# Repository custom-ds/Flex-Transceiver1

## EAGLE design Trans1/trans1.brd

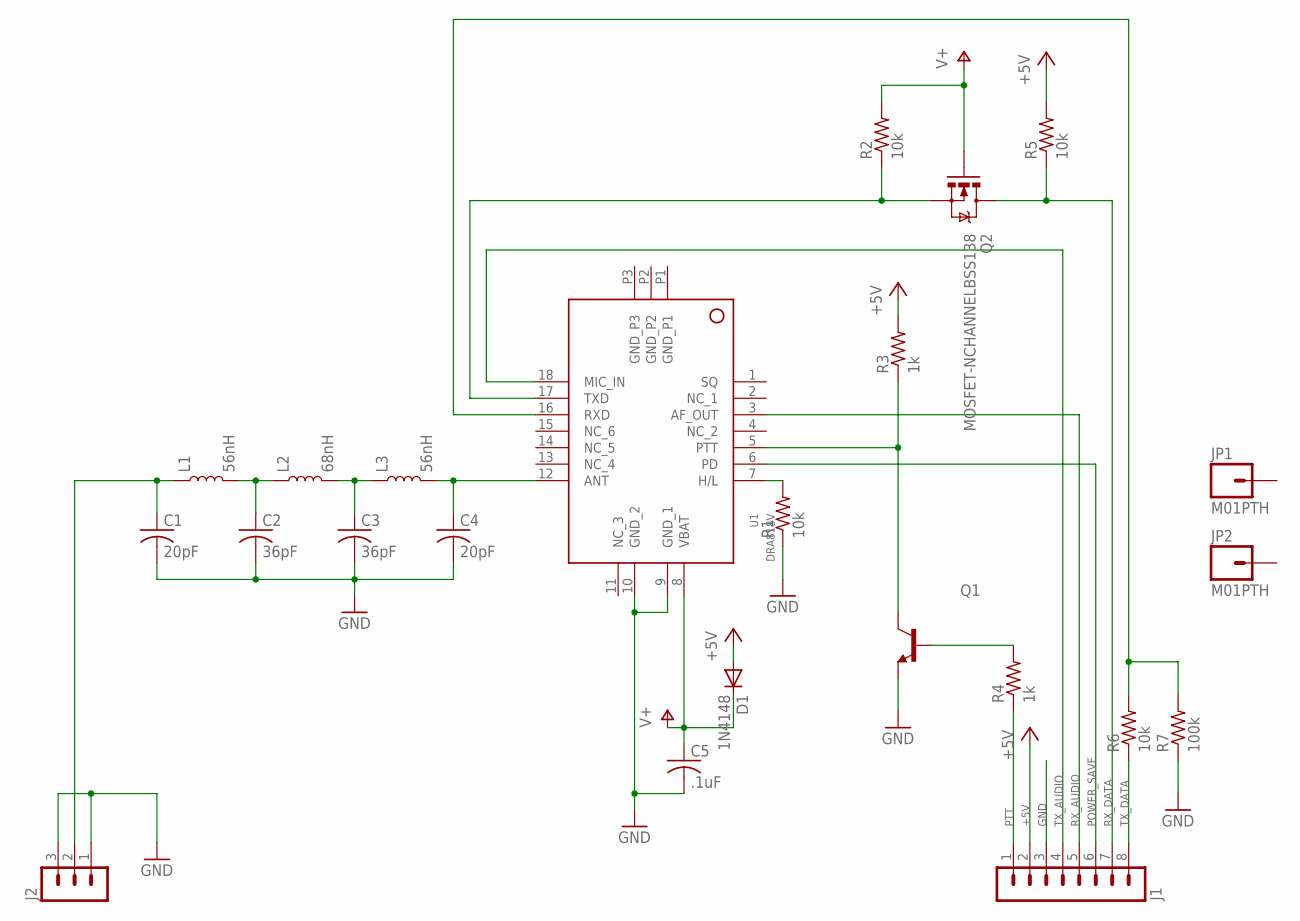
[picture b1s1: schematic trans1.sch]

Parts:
C1, C4: 20pF; C0805; DIGIKEY ‎712-1381-1-ND‎
C2, C3: 36pF; C0805; DIGIKEY 478-10473-1-ND
C5: .1uF; C0805
D1: 1N4148; SOD123
J1: MA08-1
J2: MA03-1
JP1, JP2: M01PTH; 1X01
L1, L3: 56nH; L0805; DIGIKEY 535-11570-1-ND
L2: 68nH; L0805; DIGIKEY ‎535-11572-1-ND‎
Q1: BC817-16LT1SMD; SOT23-BEC; DIGIKEY MMBT2222AFSCT-ND
Q2: MOSFET-NCHANNELBSS138; SOT23
R1, R2, R5, R6: 10k; R0805
R3, R4: 1k; R0805
R7: 100k; R0805
U1: DRA818V; SMD_DRA818

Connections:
+5V: D1.A, J1.2, R3.2, R5.2
GND: C1.2, C2.2, C3.2, C4.2, C5.2, J1.3, J2.1, J2.3, Q1.E, R1.1, R7.1, U1.9 (GND_1), U1.10 (GND_2)
unnamed: Q1.C, R3.1, U1.5 (PTT)
unnamed: R1.2, U1.7 (H/L)
unnamed: R6.2, R7.2, U1.16 (RXD)
unnamed: Q2.2 (S), R2.1, U1.17 (TXD)
unnamed: Q1.B, R4.2
unnamed: C4.1, L3.2, U1.12 (ANT)
unnamed: C3.1, L2.2, L3.1
unnamed: C2.1, L1.2, L2.1
unnamed: C1.1, J2.2, L1.1
POWER_SAVE: J1.6, U1.6 (PD)
PTT: J1.1, R4.1
RX_AUDIO: J1.5, U1.3 (AF_OUT)
RX_DATA: J1.7, Q2.3 (D), R5.1
TX_AUDIO: J1.4, U1.18 (MIC_IN)
TX_DATA: J1.8, R6.1
V+: C5.1, D1.C, Q2.1 (G), R2.2, U1.8 (VBAT)

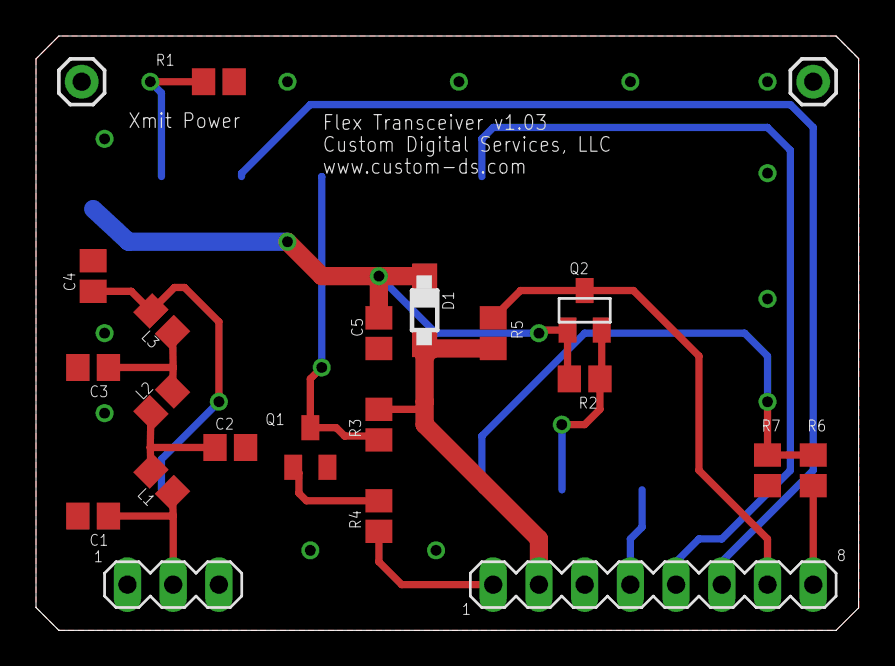
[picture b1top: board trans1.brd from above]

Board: 2 copper layers, 45.7 x 33.0 mm, 23 parts (1 on the bottom side), 18 nets.

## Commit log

2019-04-14 Version 1.03
    Added third pole to RF filter, adjusted pad size on DRA module.
2019-04-26 Updating part values

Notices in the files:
parts and their libraries:
SparkFun-DiscreteSemi: Licensing: CC v3.0 Share-Alike You are welcome to use this library for commercial purposes.
